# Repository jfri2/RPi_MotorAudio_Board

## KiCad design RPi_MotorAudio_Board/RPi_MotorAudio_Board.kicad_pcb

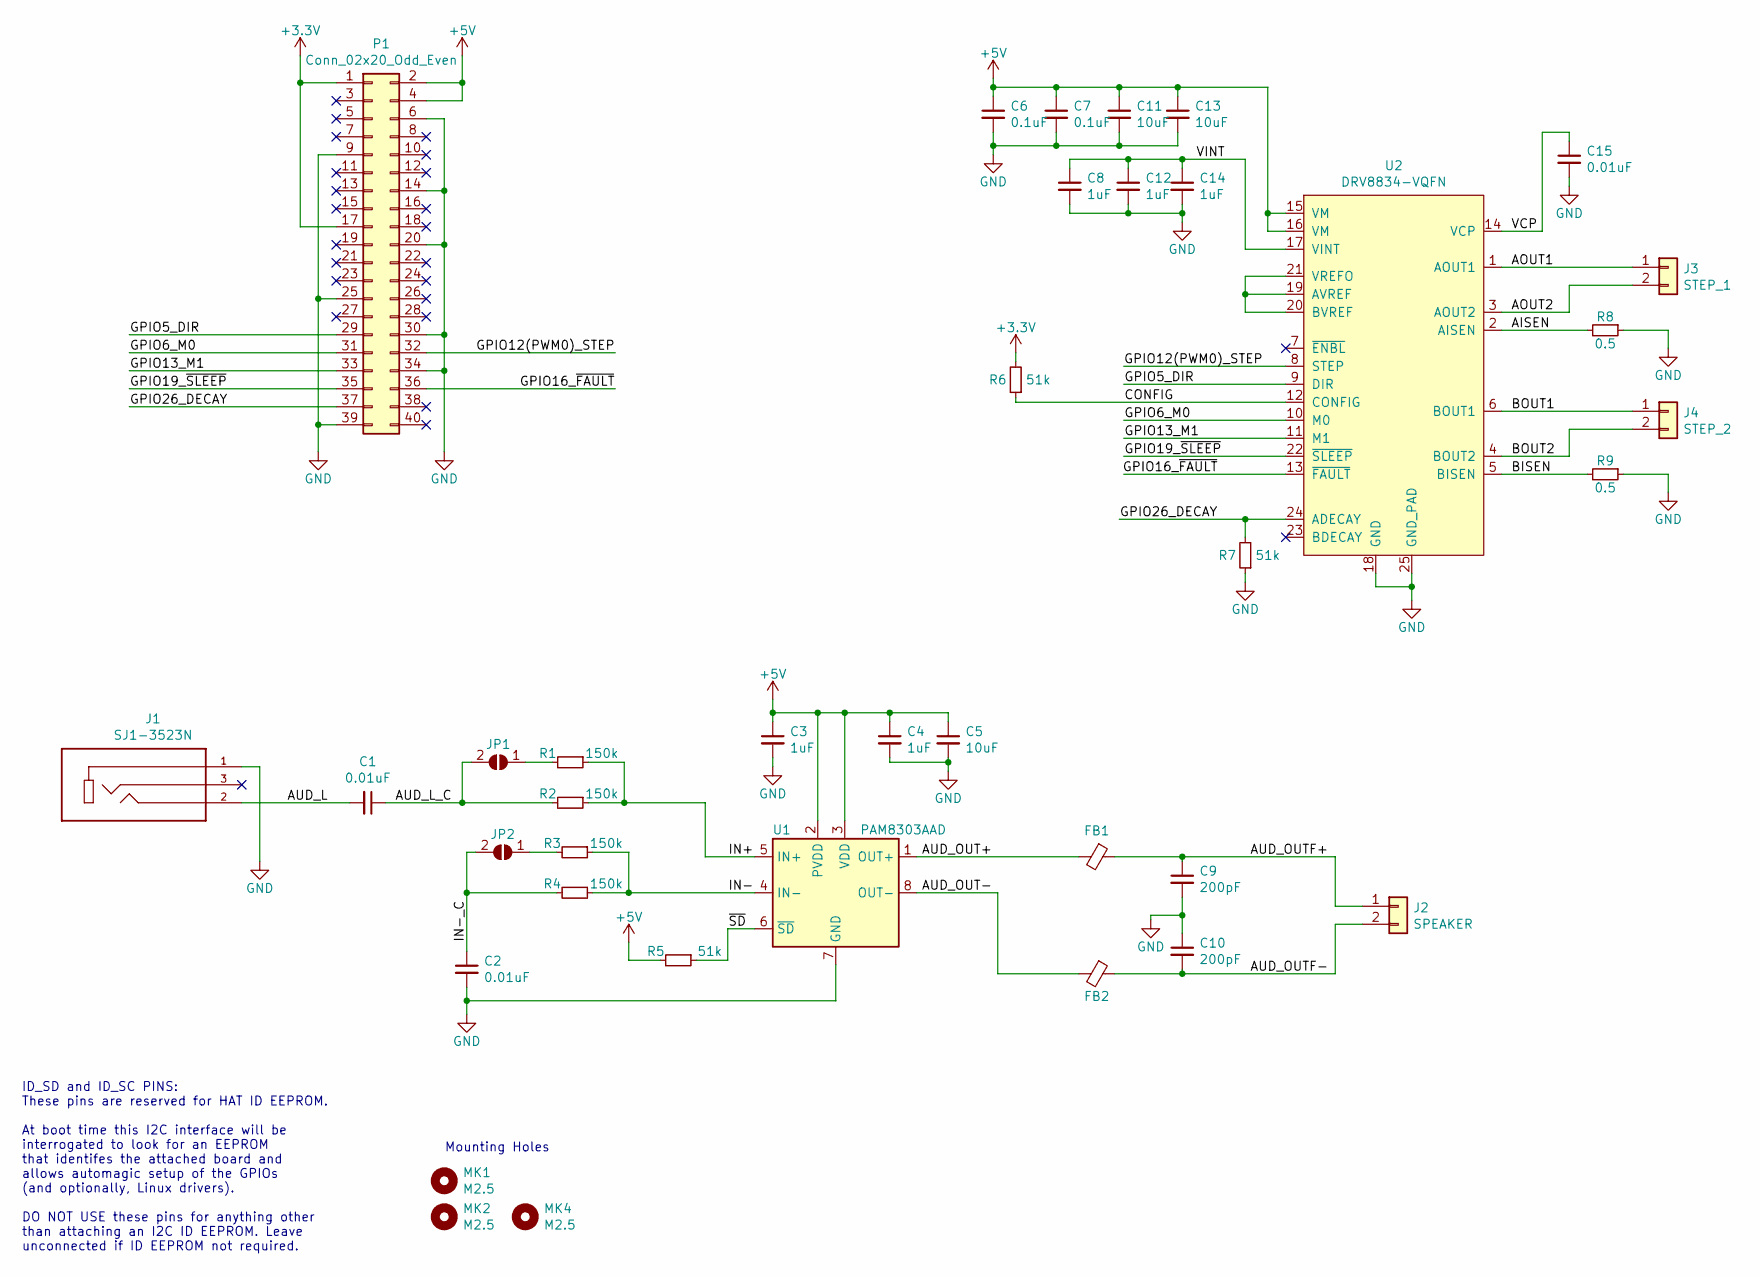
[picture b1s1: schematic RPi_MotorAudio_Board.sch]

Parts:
C1, C2, C15: 0.01uF; C_0603; JLCPCB C57112
C3, C4, C8, C12, C14: 1uF; C_0603; JLCPCB C15849
C5, C11, C13: 10uF; C_0805; JLCPCB C15850
C6, C7: 0.1uF; C_0603; JLCPCB C14663
C9, C10: 200pF; C_0603; JLCPCB C1600
FB1, FB2: Ferrite_Bead_Small; C_0603; JLCPCB C85832
J1: SJ1-3523N; CUI_SJ1-3523N
J2: SPEAKER; TerminalBlock_bornier-2_P5.08mm
J3: STEP_1; TerminalBlock_bornier-2_P5.08mm
J4: STEP_2; TerminalBlock_bornier-2_P5.08mm
JP1, JP2: SolderJumper_2_Open; Inductor_SMD_3.0mm_x_3.0mm
MK1, MK2, MK4: M2.5; MountingHole_2.7mm_M2.5
P1: Conn_02x20_Odd_Even; PinSocket_2x20_P2.54mm_Vertical
R1, R2, R3, R4: 150k; C_0603; JLCPCB C22807
R5, R6, R7: 51k; C_0603; JLCPCB C23196
R8, R9: 0.5; R_2512; JLCPCB C27777
U1: PAM8303AAD; MSOP-8_3x3mm_Pitch0.65mm; JLCPCB C56211
U2: DRV8834-VQFN; QFN50P400X400X100-25N; JLCPCB C87672

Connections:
+3V3: P1.1, P1.17, R6.2
+5V: C3.1, C4.1, C5.1, C6.1, C7.1, C11.1, C13.1, P1.2, P1.4, R5.2, U1.2 (PVDD), U1.3 (VDD), U2.15 (VM), U2.16 (VM)
/AISEN: R8.2, U2.2 (AISEN)
/AOUT1: J3.1, U2.1 (AOUT1)
/AOUT2: J3.2, U2.3 (AOUT2)
/AUD_L: C1.2, J1.2
/AUD_L_C: C1.1, JP1.2 (B), R2.2
/AUD_OUT+: FB1.2, U1.1 (OUT+)
/AUD_OUT-: FB2.2, U1.8 (OUT-)
/AUD_OUTF+: C9.1, FB1.1, J2.1
/AUD_OUTF-: C10.2, FB2.1, J2.2
/BISEN: R9.2, U2.5 (BISEN)
/BOUT1: J4.1, U2.6 (BOUT1)
/BOUT2: J4.2, U2.4 (BOUT2)
/CONFIG: R6.1, U2.12 (CONFIG)
/GPIO5_DIR: P1.29, U2.9 (DIR)
/GPIO6_M0: P1.31, U2.10 (M0)
/GPIO12(PWM0)_STEP: P1.32, U2.8 (STEP)
/GPIO13_M1: P1.33, U2.11 (M1)
/GPIO16_~FAULT: P1.36, U2.13 (~FAULT)
/GPIO19_~SLEEP: P1.35, U2.22 (~SLEEP)
/GPIO26_DECAY: P1.37, R7.2, U2.24 (ADECAY)
/IN+: R1.1, R2.1, U1.5 (IN+)
/IN-: R3.1, R4.1, U1.4 (IN-)
/IN-_C: C2.1, JP2.2 (B), R4.2
/VCP: C15.1, U2.14 (VCP)
/VINT: C8.1, C12.1, C14.1, U2.17 (VINT)
/~SD: R5.1, U1.6 (~SD)
GND: C2.2, C3.2, C4.2, C5.2, C6.2, C7.2, C8.2, C9.2, C10.1, C11.2, C12.2, C13.2, C14.2, C15.2, J1.1, P1.6, P1.9, P1.14, P1.20, P1.25, P1.30, P1.34, P1.39, R7.1, R8.1, R9.1, U1.7 (GND), U2.18 (GND), U2.25 (GND_PAD)
unnamed: JP1.1 (A), R1.2
unnamed: JP2.1 (A), R3.2
unnamed: U2.19 (AVREF), U2.20 (BVREF), U2.21 (VREFO)

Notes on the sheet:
ID_SD and ID_SC PINS: These pins are reserved for HAT ID EEPROM. At boot time this I2C interface will be interrogated to look for an EEPROM that identifes the attached board and allows automagic setup of the GPIOs (and optionally, Linux drivers). DO NOT USE these pins for anything other than attach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
Mounting Holes

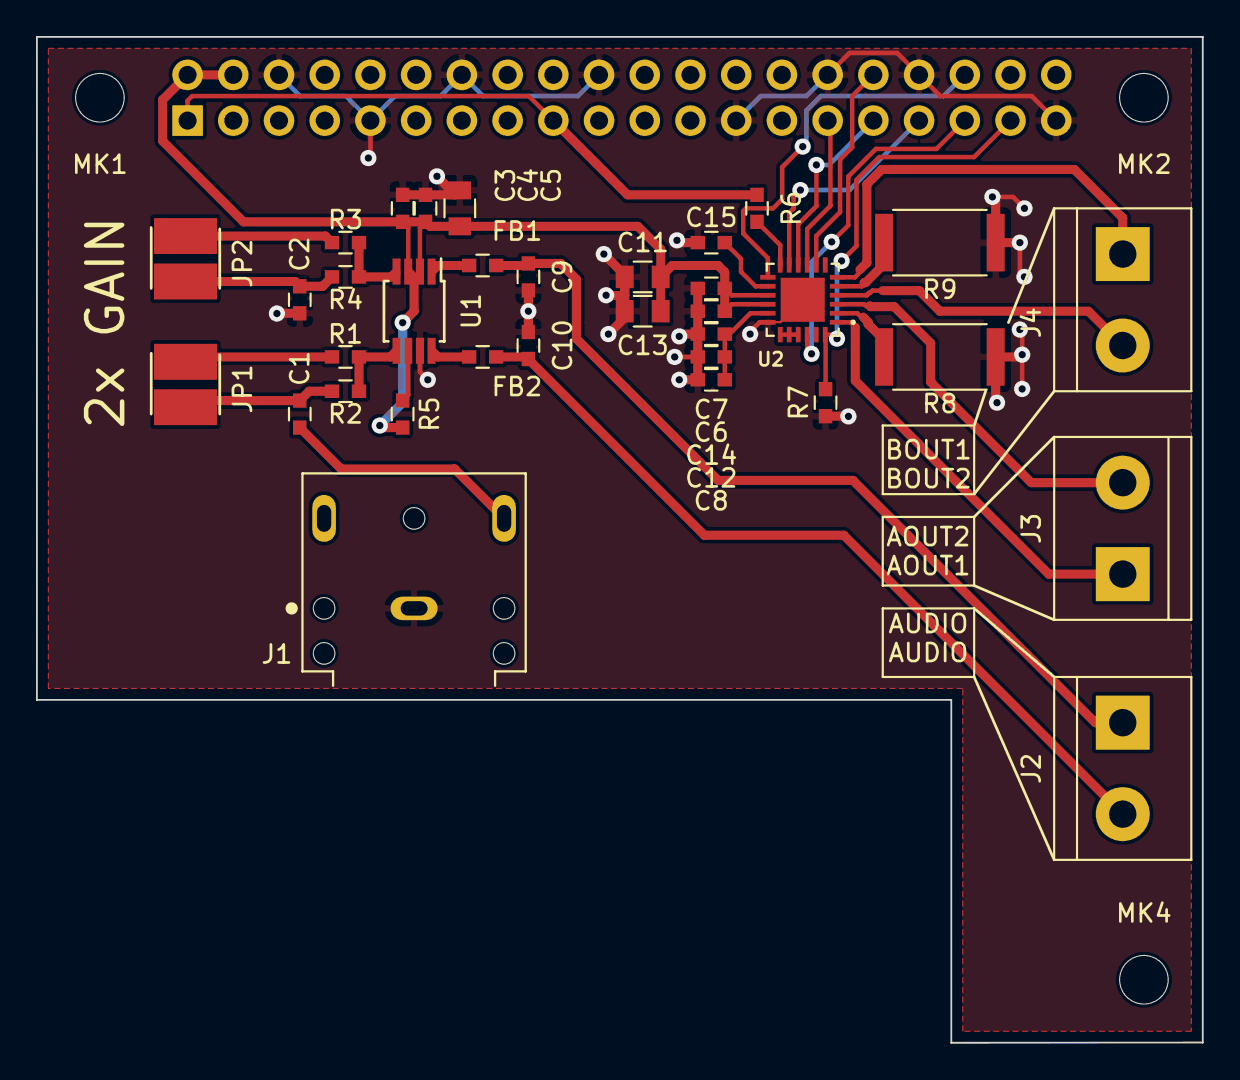
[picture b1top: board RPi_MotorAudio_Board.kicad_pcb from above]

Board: 2 copper layers, 64.8 x 55.9 mm, 38 parts (1 on the bottom side), 32 nets.

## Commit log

2020-06-14 inital commit - schematic mostly done
2020-06-14 finished component associatoin
2020-06-14 initial layout
2020-06-16 final commit before fab
